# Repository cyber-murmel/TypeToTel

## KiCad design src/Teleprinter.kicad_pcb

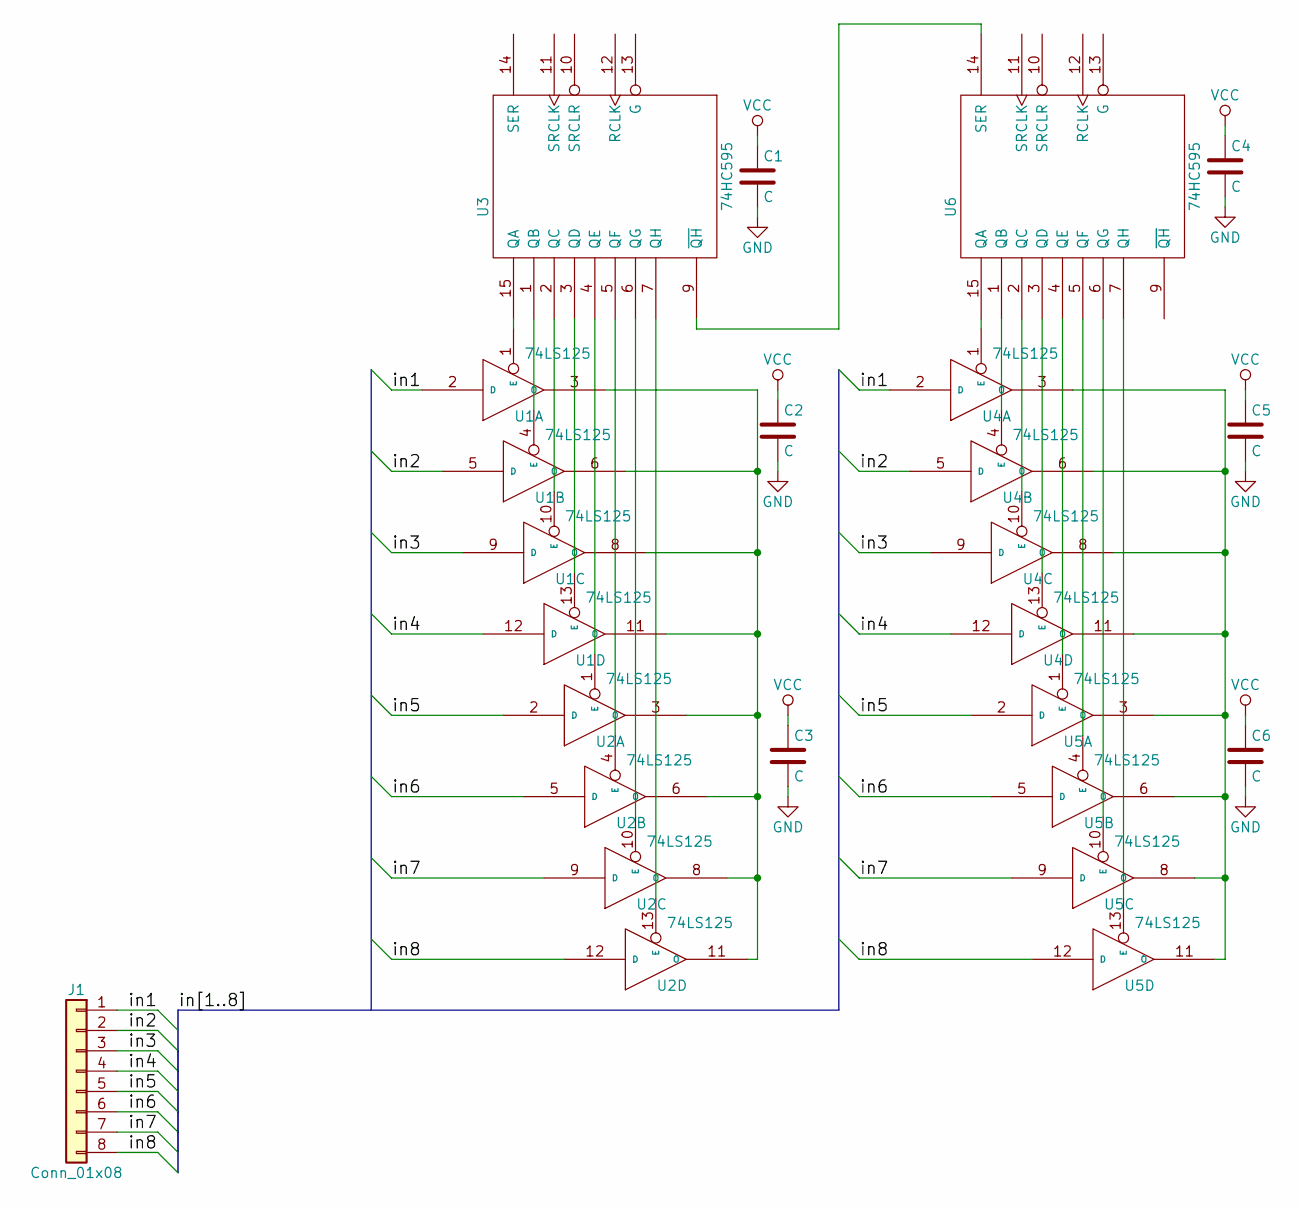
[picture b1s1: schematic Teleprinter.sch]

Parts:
C1, C2, C3, C4, C5, C6: C; C_0603_HandSoldering
J1: Conn_01x08; Pin_Header_Straight_1x08_Pitch2.54mm
U1, U2, U4, U5: 74LS125; SOIC-14_3.9x8.7mm_Pitch1.27mm
U3, U6: 74HC595; SOIC-16_3.9x9.9mm_Pitch1.27mm

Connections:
/in1: J1.1, U1.2 (D), U4.2 (D)
/in2: J1.2, U1.5 (D), U4.5 (D)
/in3: J1.3, U1.9 (D), U4.9 (D)
/in4: J1.4, U1.12 (D), U4.12 (D)
/in5: J1.5, U2.2 (D), U5.2 (D)
/in6: J1.6, U2.5 (D), U5.5 (D)
/in7: J1.7, U2.9 (D), U5.9 (D)
/in8: J1.8, U2.12 (D), U5.12 (D)
GND: C1.2, C2.2, C3.2, C4.2, C5.2, C6.2, U1.7 (GND), U2.7 (GND), U3.8 (GND), U4.7 (GND), U5.7 (GND), U6.8 (GND)
unnamed: U1.1 (E), U3.15 (QA)
unnamed: U1.4 (E), U3.1 (QB)
unnamed: U1.10 (E), U3.2 (QC)
unnamed: U1.3 (O), U1.6 (O), U1.8 (O), U1.11 (O), U2.3 (O), U2.6 (O), U2.8 (O), U2.11 (O)
unnamed: U1.13 (E), U3.3 (QD)
unnamed: U2.1 (E), U3.4 (QE)
unnamed: U2.4 (E), U3.5 (QF)
unnamed: U2.10 (E), U3.6 (QG)
unnamed: U2.13 (E), U3.7 (QH)
unnamed: U3.9 (~QH), U6.14 (SER)
unnamed: U4.1 (E), U6.15 (QA)
unnamed: U4.4 (E), U6.1 (QB)
unnamed: U4.10 (E), U6.2 (QC)
unnamed: U4.3 (O), U4.6 (O), U4.8 (O), U4.11 (O), U5.3 (O), U5.6 (O), U5.8 (O), U5.11 (O)
unnamed: U4.13 (E), U6.3 (QD)
unnamed: U5.1 (E), U6.4 (QE)
unnamed: U5.4 (E), U6.5 (QF)
unnamed: U5.10 (E), U6.6 (QG)
unnamed: U5.13 (E), U6.7 (QH)
VCC: C1.1, C2.1, C3.1, C4.1, C5.1, C6.1, U1.14 (VCC), U2.14 (VCC), U3.16 (VCC), U4.14 (VCC), U5.14 (VCC), U6.16 (VCC)

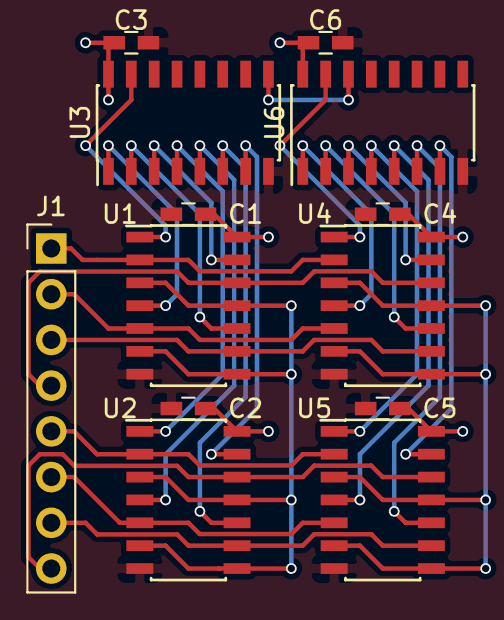
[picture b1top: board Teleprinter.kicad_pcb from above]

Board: 2 copper layers, 13 parts (0 on the bottom side), 29 nets.

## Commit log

2018-02-24 WIP: tristate buffer switch simulation.
